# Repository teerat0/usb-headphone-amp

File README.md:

# usb-headphone-amp

Three revisions of a USB headphone amp / soundcard that I made in KiCad.

Each folder has the KiCad files (schematic + PCB). V3 also has the STM32 firmware.

## The versions

**V1** (`v1/NE5532_Headphoneamp`)
- USB to I2S bridge: TI PCM2706
- I2S DAC: TI PCM5102
- Amp stages: TI NE5532
  
**V1** (`v1/Headphoneamp_psu`)
- Separate power board project for V1 amplifier: TI TPS65131 makes +-15V, then linear regulators bring it down to +-12V

**V2** (`v2/`)
- Same digital stage as V1 (PCM2706 + PCM5102)
- New analog stage: TI OPA1656 for gain, TI BUF634 as the output buffer
- Power supply is now TI LM27762, on the same board.
- Much smaller footprint

**V3 (Work in progress)** (`v3/`)
- Same as V2, but some small PCB layout changes and the PCM2706 is gone
- To get higher sample rates / bit depth, an STM32F411 does the USB audio instead (TinyUSB, UAC1.0 device)
- `v3/hardware/` = KiCad, `v3/firmware/` = STM32CubeIDE project

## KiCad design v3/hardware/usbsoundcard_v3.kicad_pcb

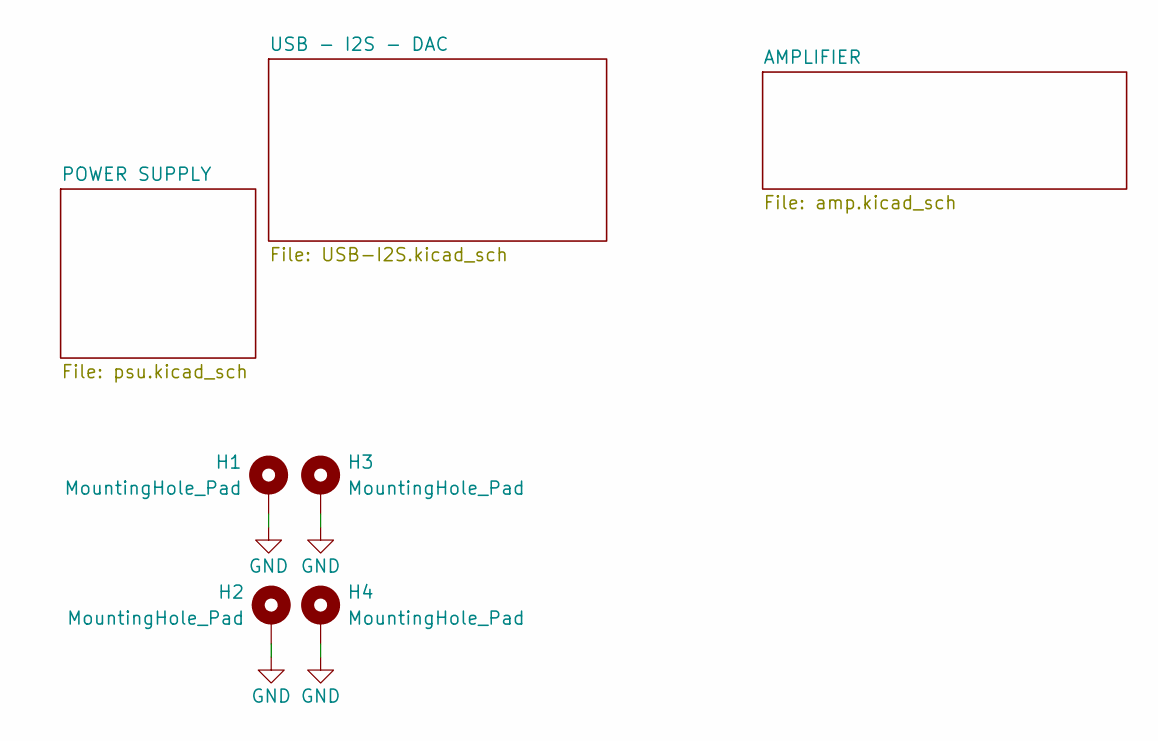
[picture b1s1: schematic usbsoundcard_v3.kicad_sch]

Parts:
H1, H2, H3, H4: MountingHole_Pad; MountingHole_3.2mm_M3_Pad_Via

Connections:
GND: H1.1 (1_1), H2.1 (1_1), H3.1 (1_1), H4.1 (1_1); also elsewhere on the board

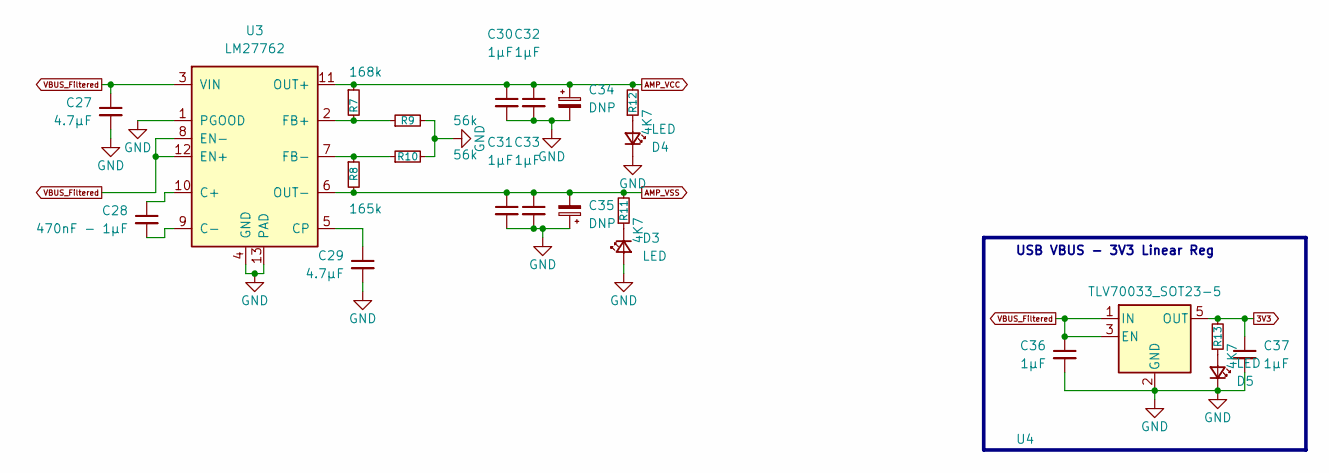
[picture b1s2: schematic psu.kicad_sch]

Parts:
C27, C29: 4.7µF; C_0603_1608Metric
C28: 470nF - 1µF; C_0603_1608Metric
C30, C31, C32, C33, C36, C37: 1µF; C_0603_1608Metric
C34, C35: DNP; CP_Radial_D10.0mm_P5.00mm
D3, D4, D5: LED; LED_0603_1608Metric
R7: 168k; R_0603_1608Metric
R8: 165k; R_0603_1608Metric
R9, R10: 56k; R_0603_1608Metric
R11, R12, R13: 4K7; R_0603_1608Metric
U3: LM27762; WSON-12-1EP_3x2mm_P0.5mm_EP1x2.65_ThermalVias
U4: TLV70033_SOT23-5; SOT-23-5

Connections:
3V3: C37.1, R13.2, U4.5 (OUT); also elsewhere on the board
AMP_VCC: C30.1, C32.1, C34.1, R7.1, R12.2, U3.11 (OUT+); also elsewhere on the board
AMP_VSS: C31.1, C33.1, C35.2, R8.2, R11.2, U3.6 (OUT-); also elsewhere on the board
GND: C27.2, C29.2, C30.2, C31.2, C32.2, C33.2, C34.2, C35.1, C36.2, C37.2, D3.2 (A), D4.1 (K), D5.1 (K), R9.2, R10.2, U3.1 (PGOOD), U3.4 (GND), U3.13 (PAD), U4.2 (GND); also elsewhere on the board
unnamed: D3.1 (K), R11.1
unnamed: D4.2 (A), R12.1
unnamed: D5.2 (A), R13.1
unnamed: C28.1, U3.10 (C+)
unnamed: C28.2, U3.9 (C-)
unnamed: C29.1, U3.5 (CP)
unnamed: R7.2, R9.1, U3.2 (FB+)
unnamed: R8.1, R10.1, U3.7 (FB-)
VBUS_Filtered: C27.1, C36.1, U3.3 (VIN), U3.8 (EN-), U3.12 (EN+), U4.1 (IN), U4.3 (EN); also elsewhere on the board

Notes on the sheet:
USB VBUS - 3V3 Linear Reg

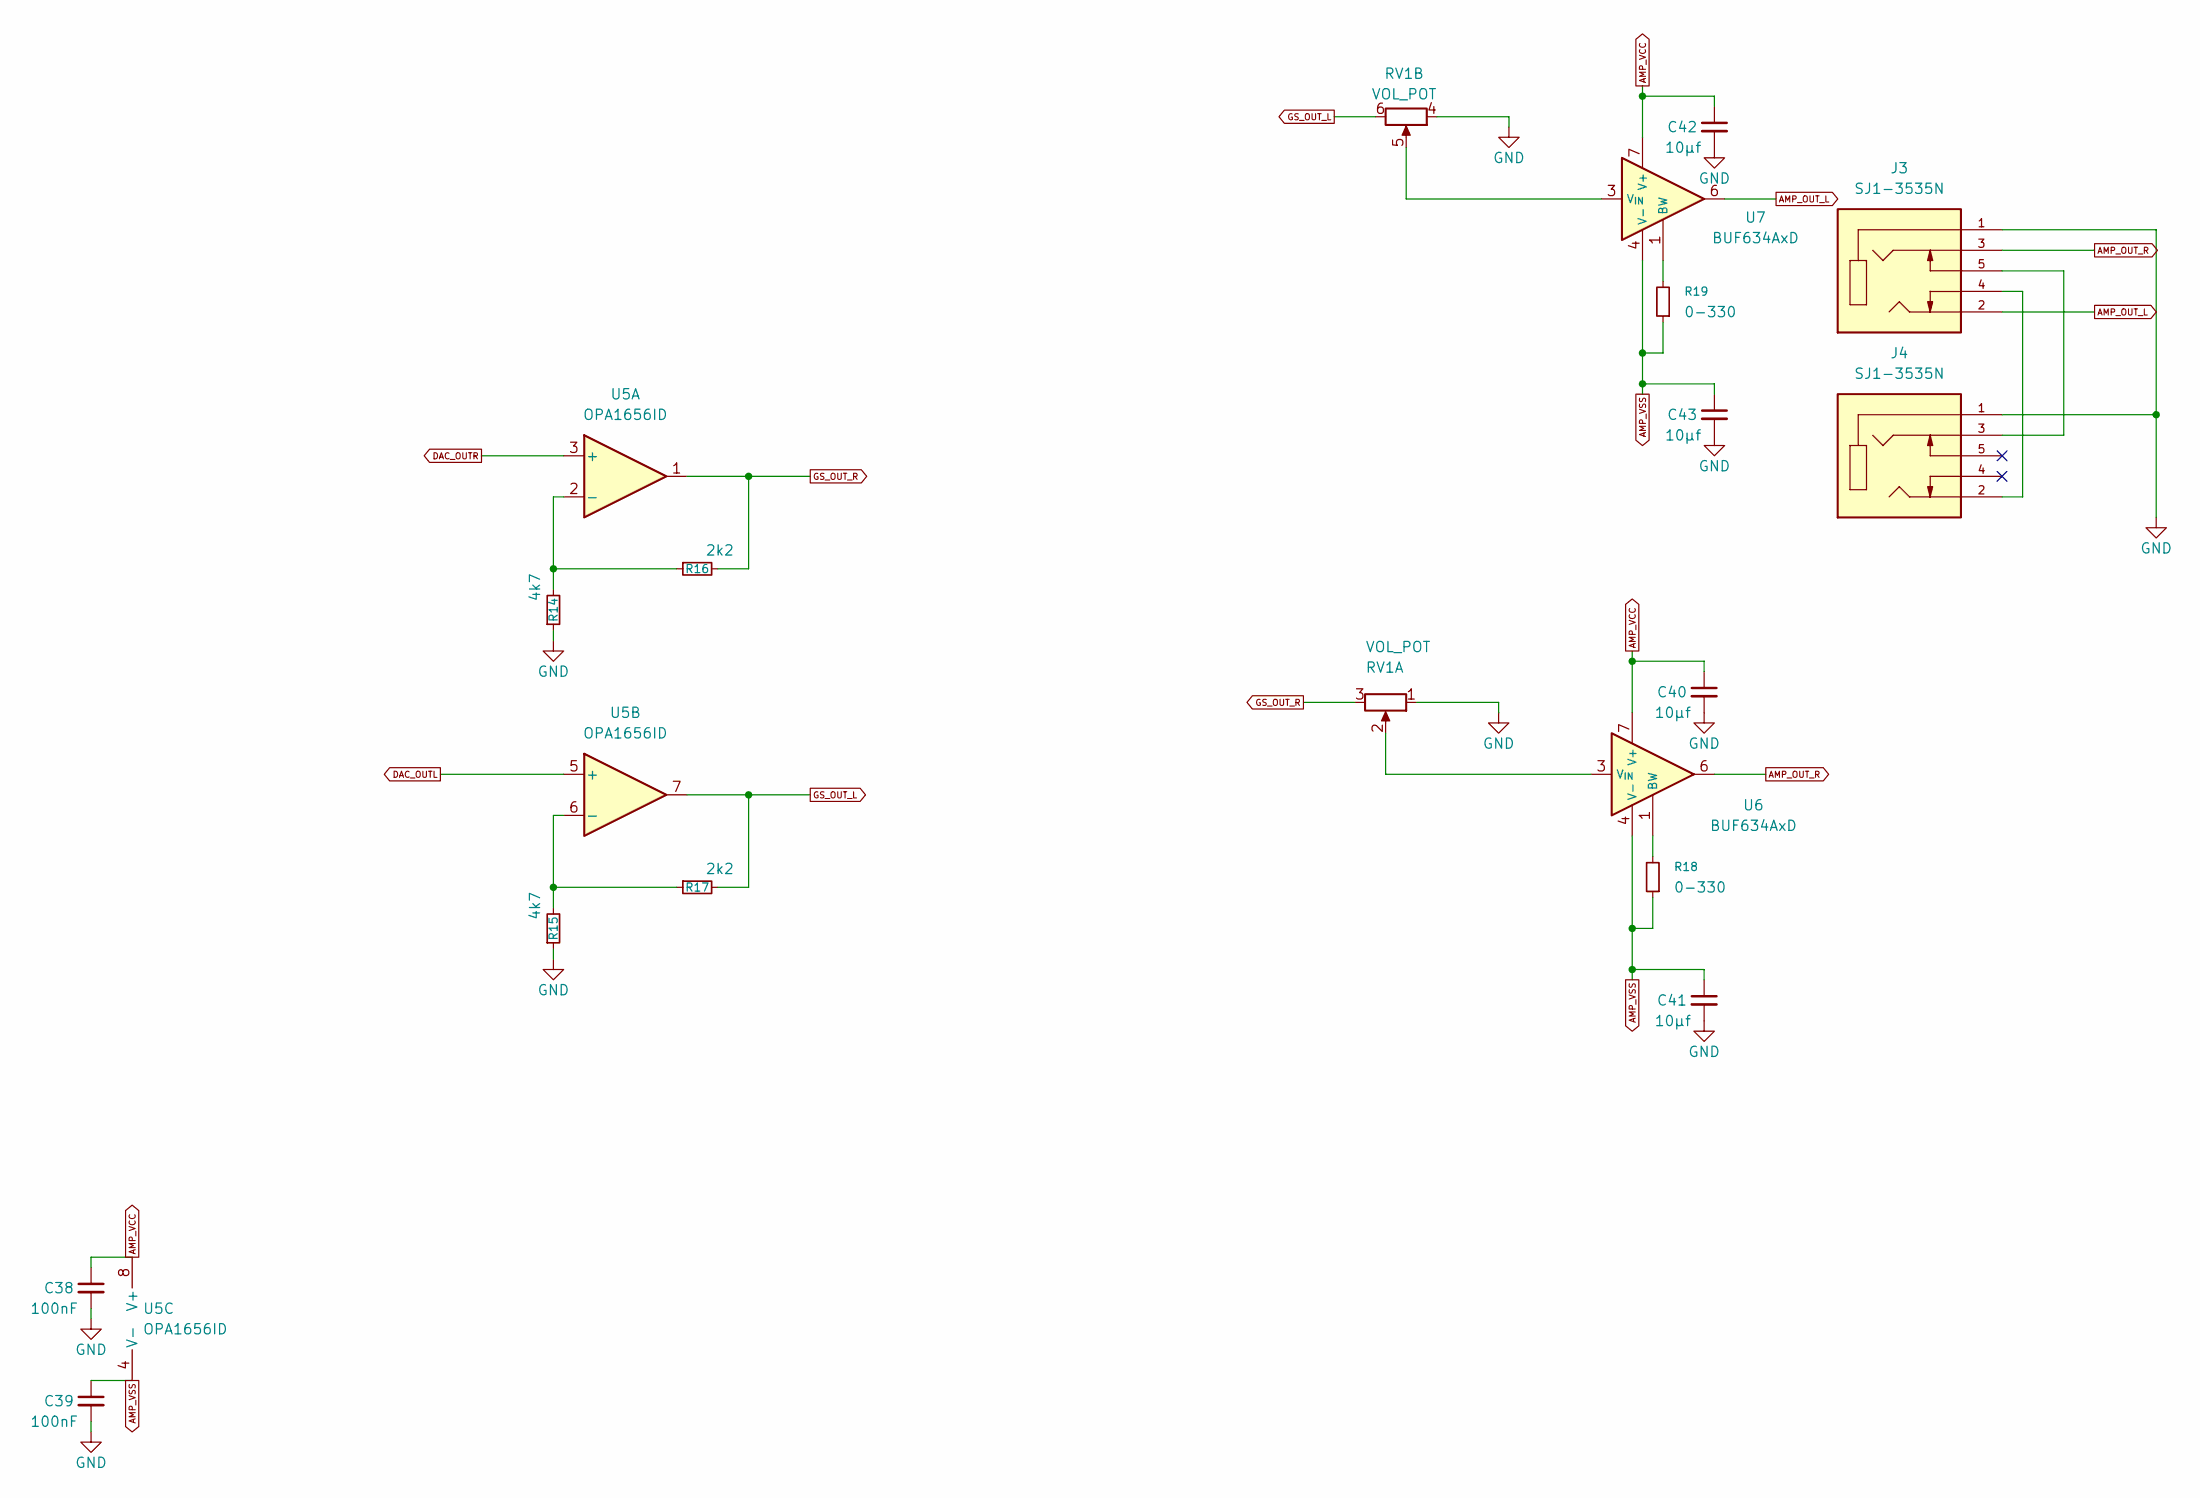
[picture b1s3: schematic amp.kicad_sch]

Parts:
C38, C39: 100nF; C_0603_1608Metric
C40, C41, C42, C43: 10µf; C_0603_1608Metric
J3, J4: SJ1-3535N; CUI_SJ1-3535N; PARTREV 1.03
R14, R15: 4k7; R_0603_1608Metric
R16, R17: 2k2; R_0603_1608Metric
R18, R19: 0-330; R_0603_1608Metric
RV1: VOL_POT; RK12L12
U5: OPA1656ID; SOIC-8_3.9x4.9mm_P1.27mm
U6, U7: BUF634AxD; SOIC-8_3.9x4.9mm_P1.27mm

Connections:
AMP_OUT_L: J3.2, U7.6
AMP_OUT_R: J3.3, U6.6
AMP_VCC: C38.1, C40.1, C42.1, U5.8 (V+), U6.7 (V+), U7.7 (V+); also elsewhere on the board
AMP_VSS: C39.1, C41.1, C43.1, R18.1, R19.1, U5.4 (V-), U6.4 (V-), U7.4 (V-); also elsewhere on the board
DAC_OUTL: U5.5 (+); also elsewhere on the board
DAC_OUTR: U5.3 (+); also elsewhere on the board
GND: C38.2, C39.2, C40.2, C41.2, C42.2, C43.2, J3.1, J4.1, R14.1, R15.1, RV1.1, RV1.4; also elsewhere on the board
GS_OUT_L: R17.2, RV1.6, U5.7
GS_OUT_R: R16.2, RV1.3, U5.1
unnamed: J3.4, J4.2
unnamed: J3.5, J4.3
unnamed: R14.2, R16.1, U5.2 (-)
unnamed: R15.2, R17.1, U5.6 (-)
unnamed: R18.2, U6.1 (BW)
unnamed: RV1.2, U6.3 (V_{IN})
unnamed: R19.2, U7.1 (BW)
unnamed: RV1.5, U7.3 (V_{IN})

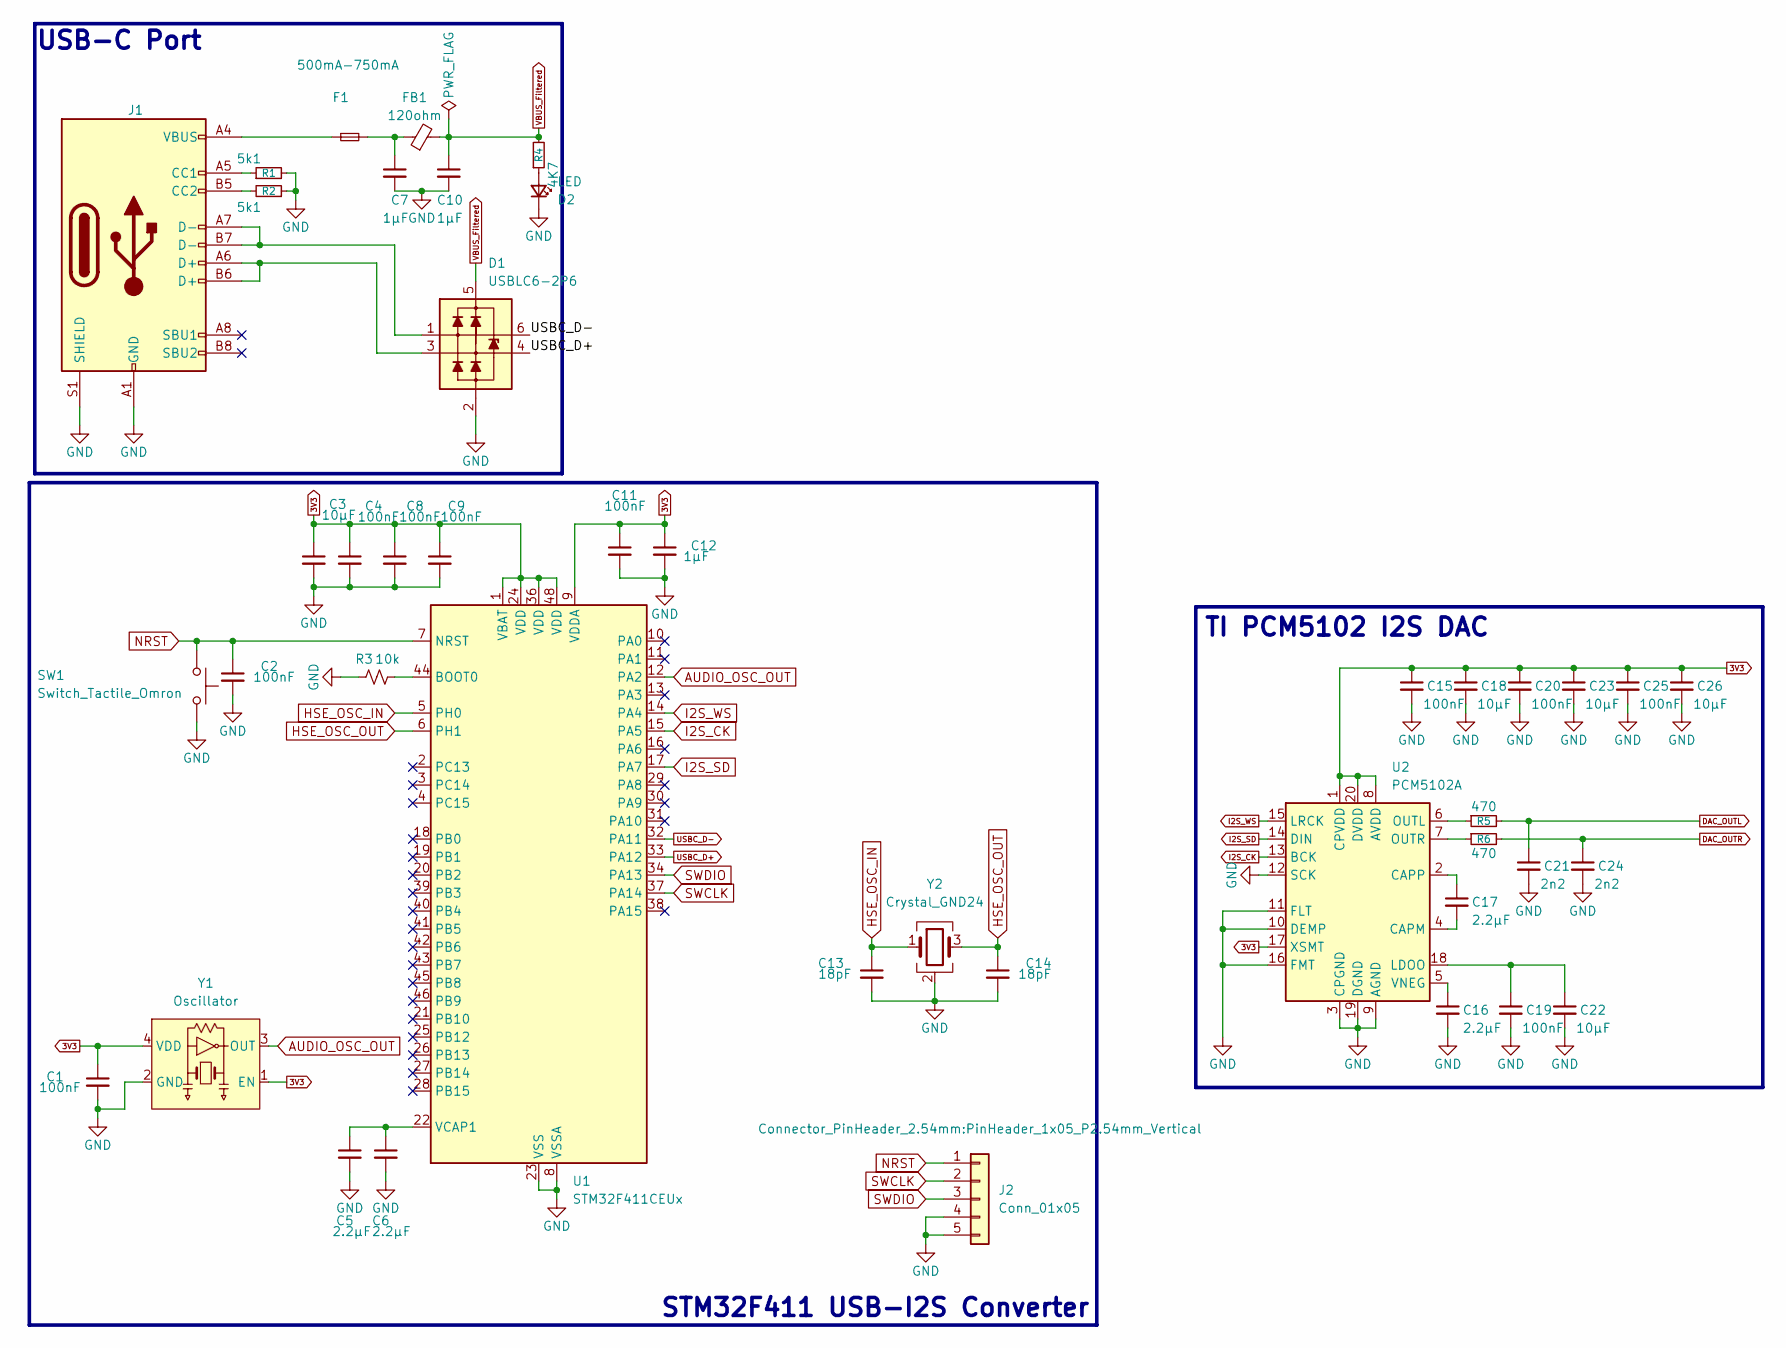
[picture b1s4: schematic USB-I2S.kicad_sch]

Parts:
C1, C2, C4, C8, C9, C11, C15, C19, C20, C25: 100nF; C_0603_1608Metric
C3, C18, C22, C23, C26: 10µF; C_0603_1608Metric
C5, C6, C16, C17: 2.2µF; C_0603_1608Metric
C7, C10, C12: 1µF; C_0603_1608Metric
C13, C14: 18pF; C_0603_1608Metric
C21, C24: 2n2; C_0603_1608Metric
D1: USBLC6-2P6; SOT-666
D2: LED; LED_0603_1608Metric
F1: 500mA-750mA; Fuse_0603_1608Metric
FB1: 120ohm; L_0603_1608Metric
J1: USB_C_Receptacle_USB2.0_16P; USB_C_Receptacle_GCT_USB4105-xx-A_16P_TopMnt_Horizontal
J2: Conn_01x05; PinHeader_1x05_P2.54mm_Vertical
R1, R2: 5k1; R_0603_1608Metric
R3: 10k; R_0603_1608Metric
R4: 4K7; R_0603_1608Metric
R5, R6: 470; R_0603_1608Metric
SW1: Switch_Tactile_Omron; Button_CnK_PTS636.0_6x3.5mm
U1: STM32F411CEUx; QFN-48-1EP_7x7mm_P0.5mm_EP5.15x5.15mm_ThermalVias
U2: PCM5102A; TSSOP-20_4.4x6.5mm_P0.65mm
Y1: Oscillator; Crystal_SMD_2520-4Pin_2.5x2.0mm
Y2: Crystal_GND24; Crystal_SMD_3225-4Pin_3.2x2.5mm

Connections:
3V3: C1.1, C3.1, C4.1, C8.1, C9.1, C11.1, C12.1, C15.1, C18.1, C20.1, C23.1, C25.1, C26.1, U1.1 (VBAT), U1.9 (VDDA), U1.24 (VDD), U1.36 (VDD), U1.48 (VDD), U2.1 (CPVDD), U2.8 (AVDD), U2.17 (XSMT), U2.20 (DVDD), Y1.1 (EN), Y1.4 (VDD); also elsewhere on the board
AUDIO_OSC_OUT: U1.12 (PA2), Y1.3 (OUT)
DAC_OUTL: C21.1, R5.2; also elsewhere on the board
DAC_OUTR: C24.1, R6.2; also elsewhere on the board
GND: C1.2, C2.2, C3.2, C4.2, C5.2, C6.2, C7.2, C8.2, C9.2, C10.2, C11.2, C12.2, C13.2, C14.2, C15.2, C16.2, C18.2, C19.2, C20.2, C21.2, C22.2, C23.2, C24.2, C25.2, C26.2, D1.2 (VN), D2.1 (K), J1.A1 (GND), J1.A12 (GND), J1.B1 (GND), J1.B12 (GND), J1.S1 (SHIELD), J2.4, J2.5, R1.2, R2.1, R3.1, SW1.2, U1.8 (VSSA), U1.23 (VSS), U1.35 (VSS), U1.47 (VSS), U1.49 (VSS), U2.3 (CPGND), U2.9 (AGND), U2.10 (DEMP), U2.11 (FLT), U2.12 (SCK), U2.16 (FMT), U2.19 (DGND), Y1.2 (GND), Y2.2 (G), Y2.4 (G); also elsewhere on the board
HSE_OSC_IN: C13.1, U1.5 (PH0), Y2.1
HSE_OSC_OUT: C14.1, U1.6 (PH1), Y2.3
I2S_CK: U1.15 (PA5), U2.13 (BCK)
I2S_SD: U1.17 (PA7), U2.14 (DIN)
I2S_WS: U1.14 (PA4), U2.15 (LRCK)
NRST: C2.1, J2.1, SW1.1, U1.7 (NRST)
unnamed: C7.1, F1.2, FB1.1
unnamed: D1.1 (L1), J1.A7 (D-), J1.B7 (D-)
unnamed: D1.3 (L2), J1.A6 (D+), J1.B6 (D+)
unnamed: D2.2 (A), R4.1
unnamed: F1.1, J1.A4 (VBUS), J1.A9 (VBUS), J1.B4 (VBUS), J1.B9 (VBUS)
unnamed: J1.A5 (CC1), R1.1
unnamed: J1.B5 (CC2), R2.2
unnamed: R3.2, U1.44 (BOOT0)
unnamed: C5.1, C6.1, U1.22 (VCAP1)
unnamed: C17.2, U2.4 (CAPM)
unnamed: C17.1, U2.2 (CAPP)
unnamed: C19.1, C22.1, U2.18 (LDOO)
unnamed: R5.1, U2.6 (OUTL)
unnamed: R6.1, U2.7 (OUTR)
unnamed: C16.1, U2.5 (VNEG)
SWCLK: J2.2, U1.37 (PA14)
SWDIO: J2.3, U1.34 (PA13)
USBC_D+: D1.4 (L2), U1.33 (PA12)
USBC_D-: D1.6 (L1), U1.32 (PA11)
VBUS_Filtered: C10.1, D1.5 (VP), FB1.2, R4.2; also elsewhere on the board

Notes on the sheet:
USB-C Port
STM32F411 USB-I2S Converter
TI PCM5102 I2S DAC

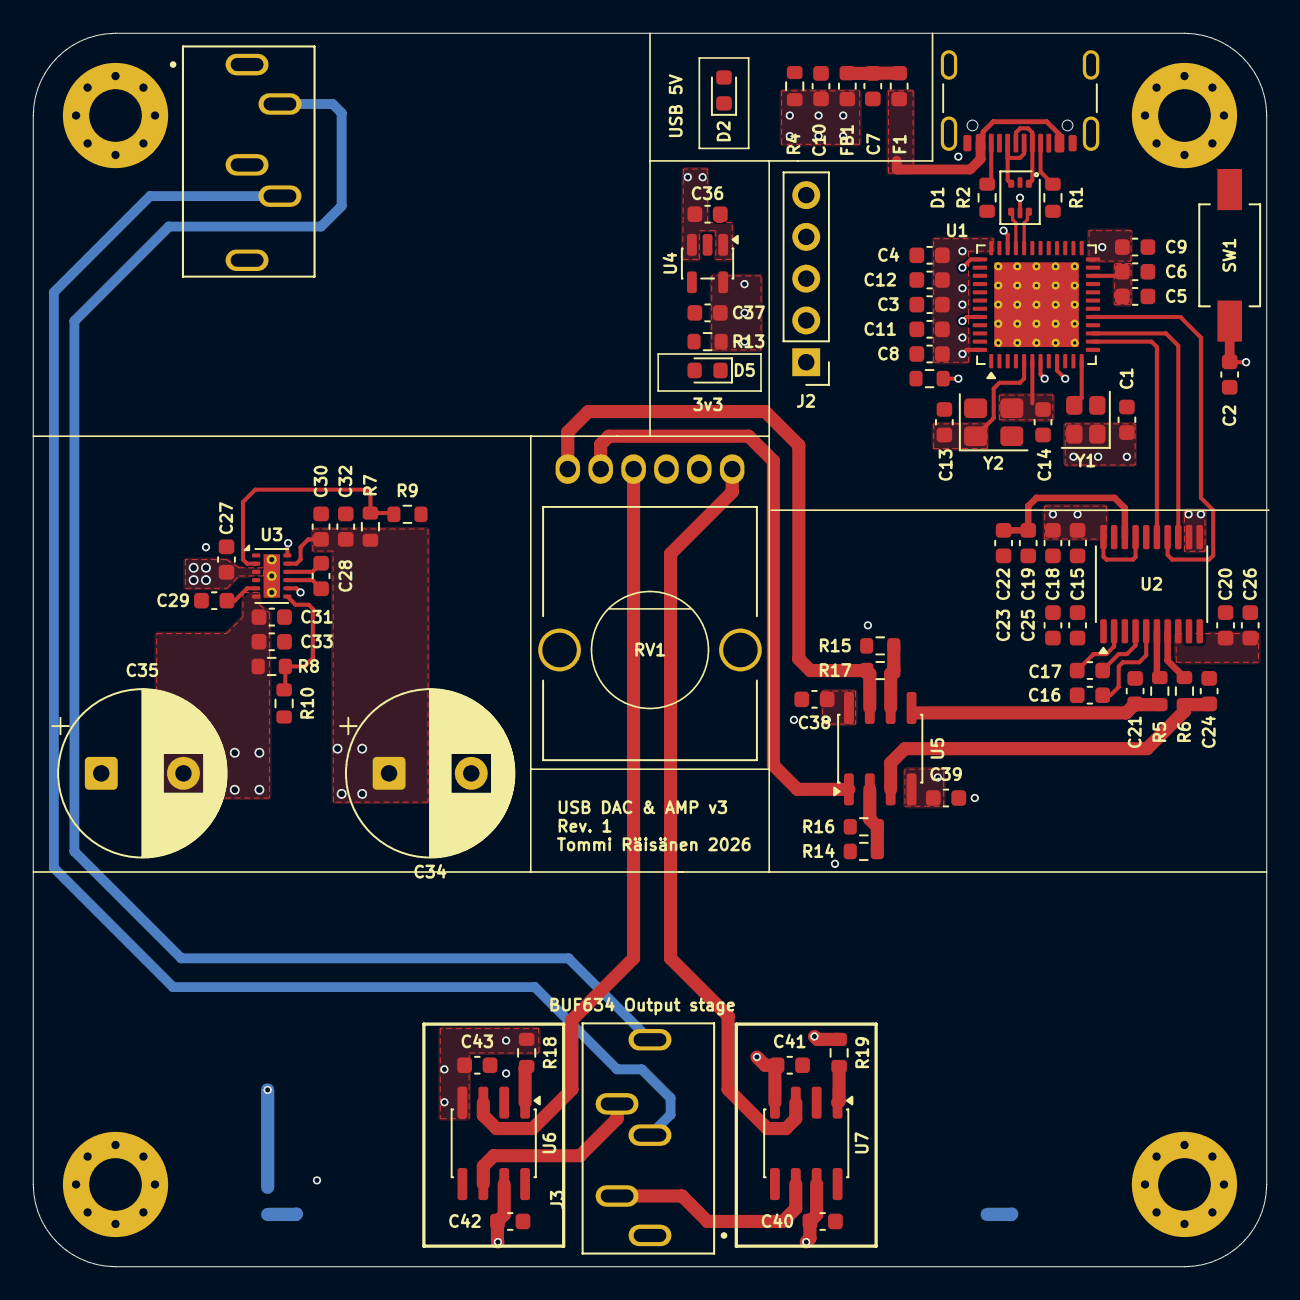
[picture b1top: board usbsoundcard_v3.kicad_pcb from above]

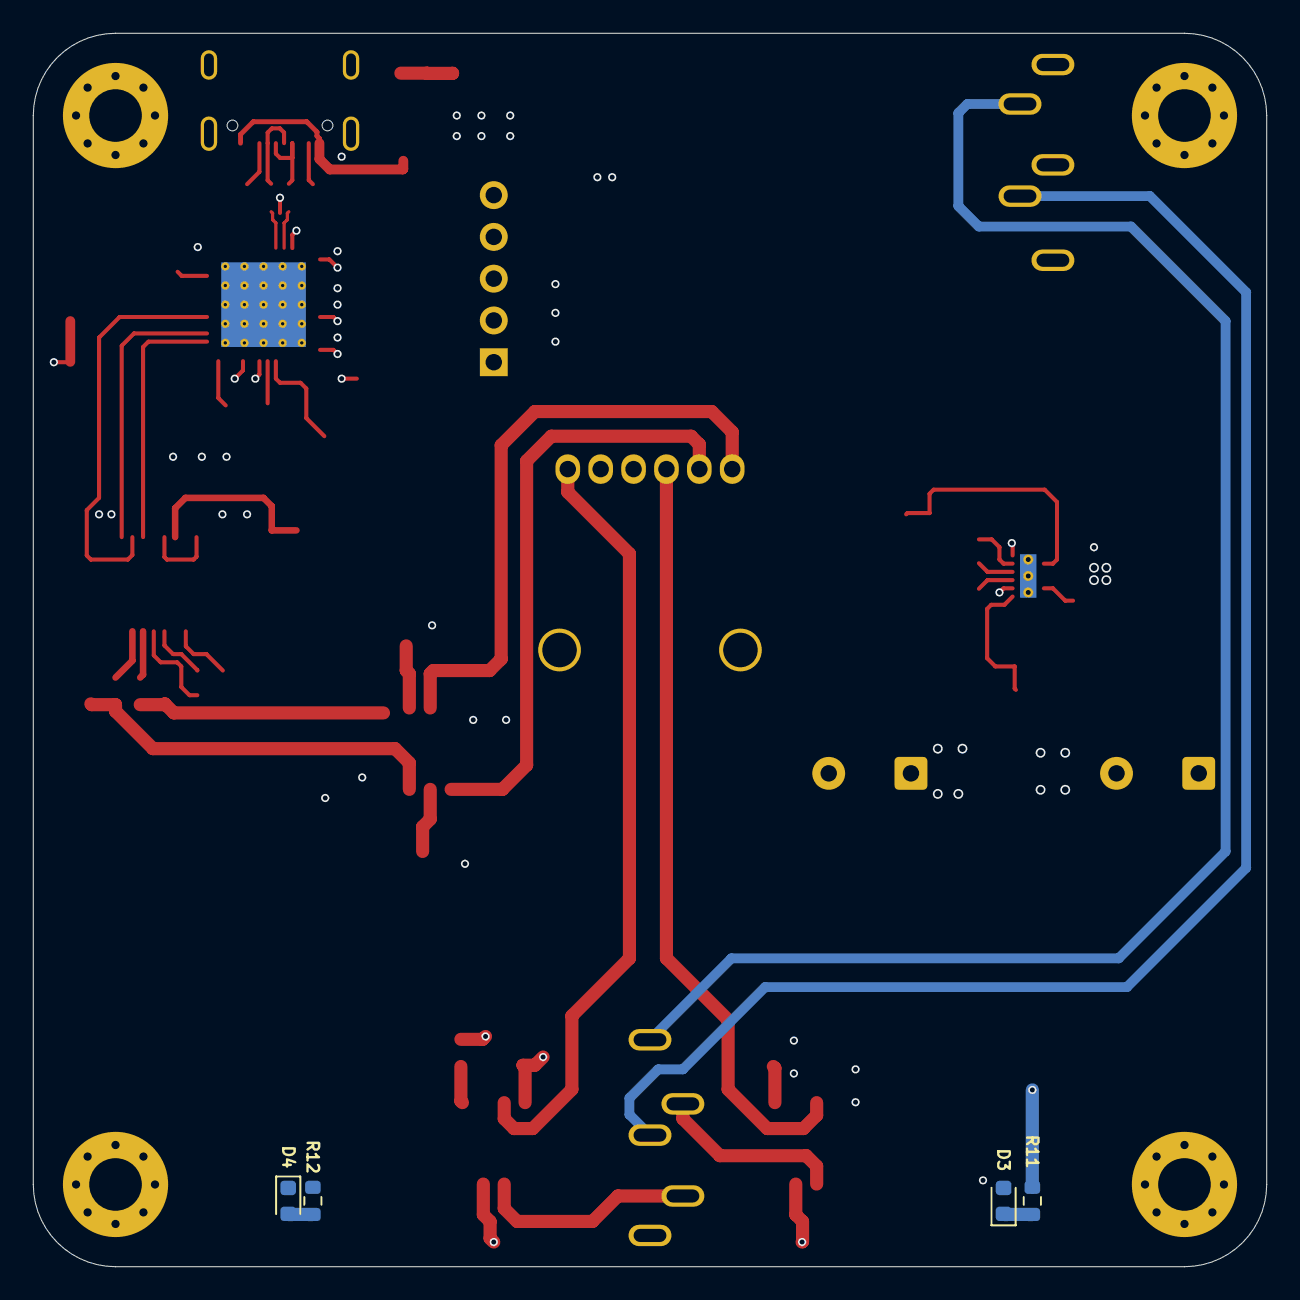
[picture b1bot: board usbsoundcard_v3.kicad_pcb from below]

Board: 4 copper layers, 75.0 x 75.0 mm, 88 parts (4 on the bottom side), 53 nets.
